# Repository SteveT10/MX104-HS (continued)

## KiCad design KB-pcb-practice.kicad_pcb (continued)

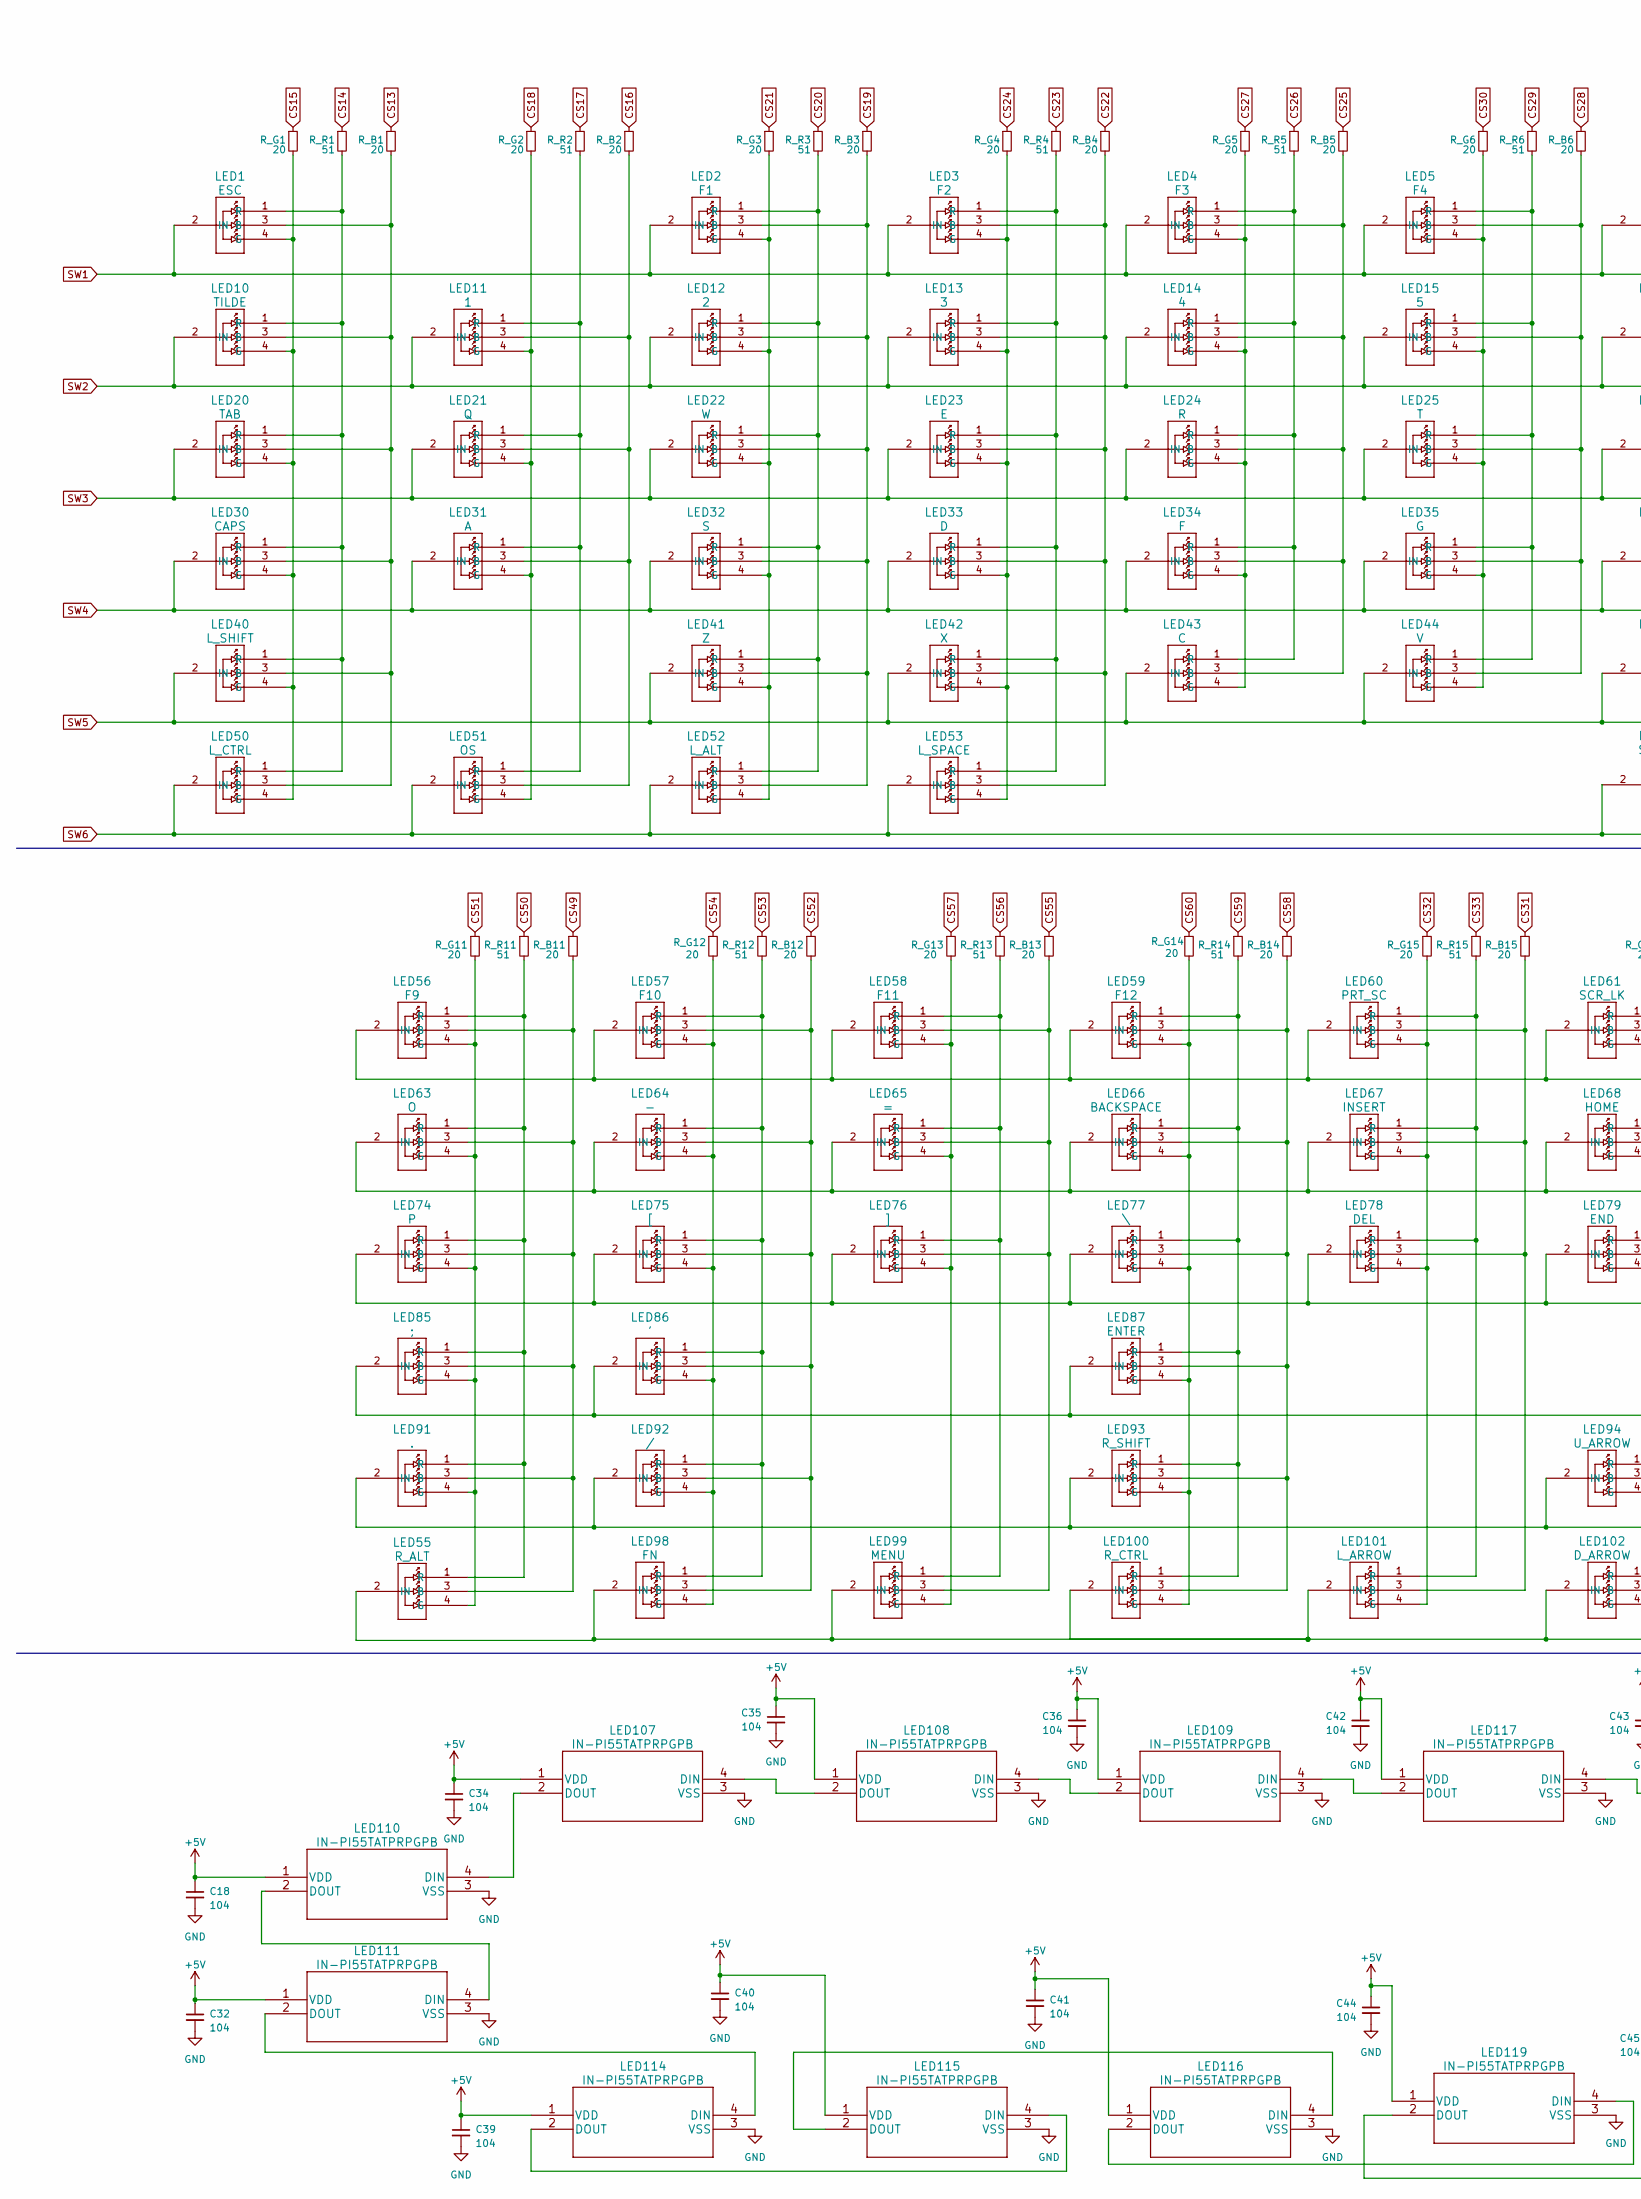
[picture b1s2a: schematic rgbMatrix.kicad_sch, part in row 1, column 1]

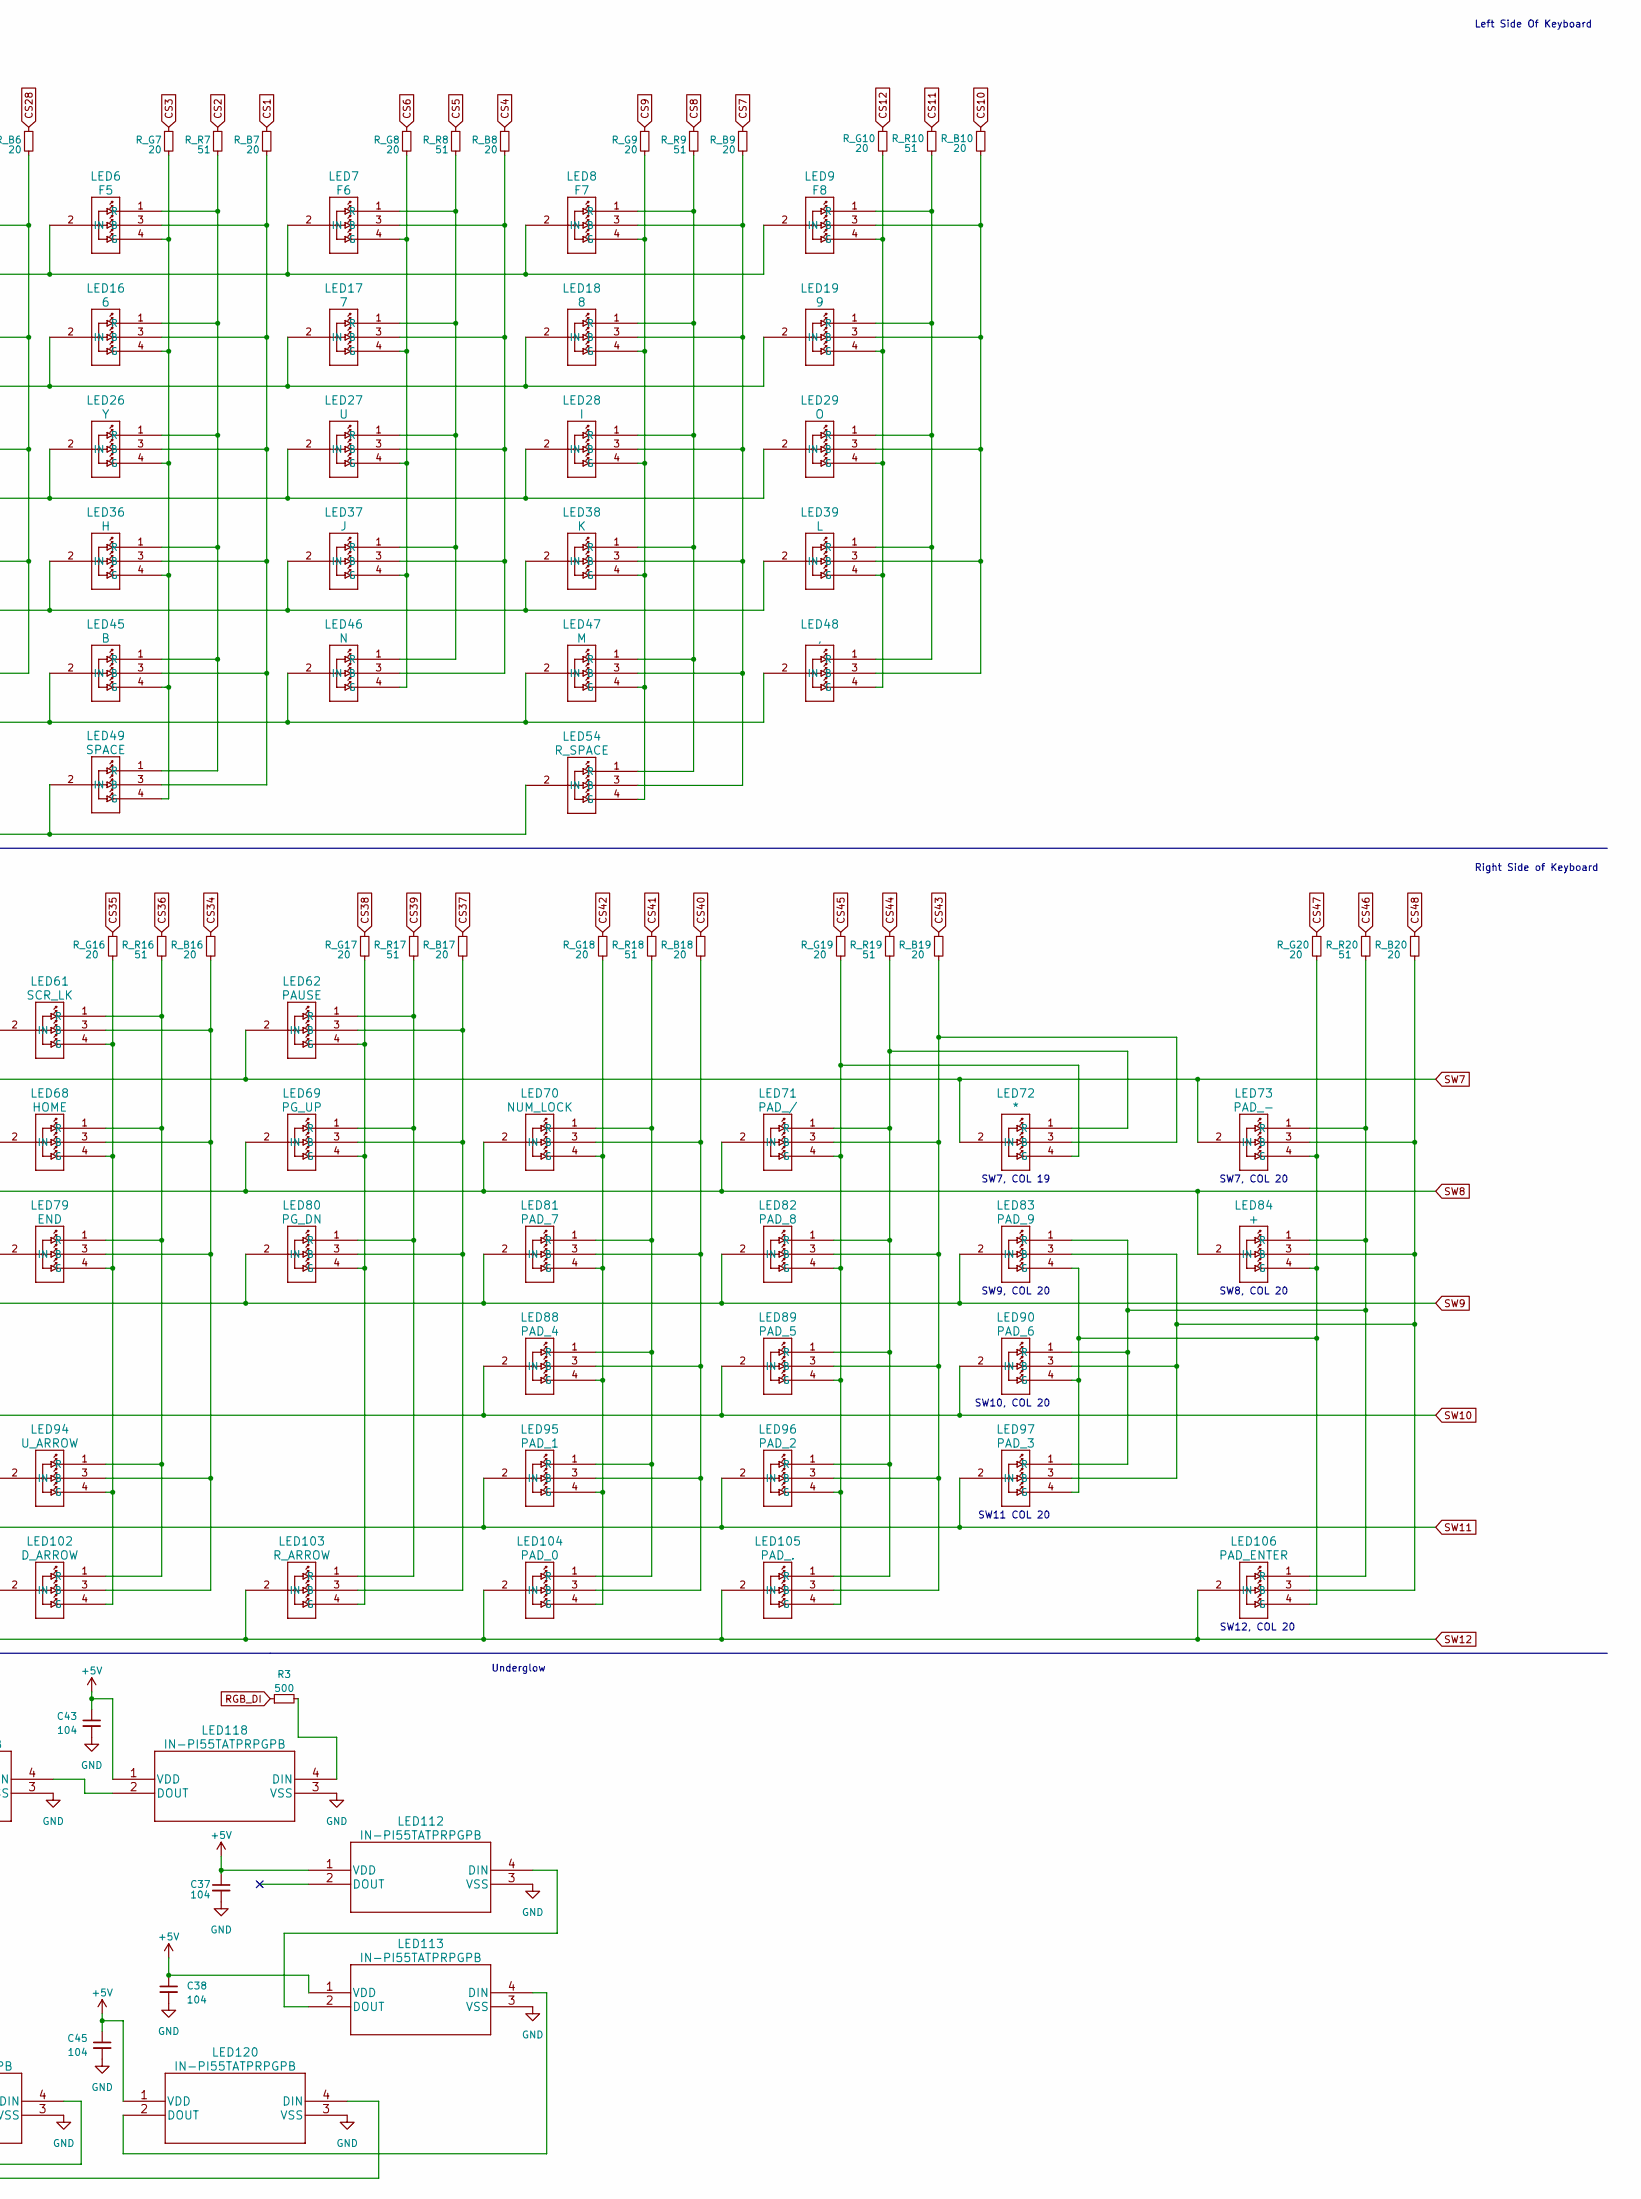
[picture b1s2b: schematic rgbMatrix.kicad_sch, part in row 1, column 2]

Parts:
C18, C32, C34, C35, C36, C37, C38, C39, C40, C41, C42, C43, C44, C45: 104; C_0805_2012Metric_Pad1.18x1.45mm_HandSolder
LED1: ESC; PLCC4_SMD-LED_3p2X2p8_SLD
LED2: F1; PLCC4_SMD-LED_3p2X2p8_SLD
LED3: F2; PLCC4_SMD-LED_3p2X2p8_SLD
LED4: F3; PLCC4_SMD-LED_3p2X2p8_SLD
LED5: F4; PLCC4_SMD-LED_3p2X2p8_SLD
LED6: F5; PLCC4_SMD-LED_3p2X2p8_SLD
LED7: F6; PLCC4_SMD-LED_3p2X2p8_SLD
LED8: F7; PLCC4_SMD-LED_3p2X2p8_SLD
LED9: F8; PLCC4_SMD-LED_3p2X2p8_SLD
LED10: TILDE; PLCC4_SMD-LED_3p2X2p8_SLD
LED11: 1; PLCC4_SMD-LED_3p2X2p8_SLD
LED12: 2; PLCC4_SMD-LED_3p2X2p8_SLD
LED13: 3; PLCC4_SMD-LED_3p2X2p8_SLD
LED14: 4; PLCC4_SMD-LED_3p2X2p8_SLD
LED15: 5; PLCC4_SMD-LED_3p2X2p8_SLD
LED16: 6; PLCC4_SMD-LED_3p2X2p8_SLD
LED17: 7; PLCC4_SMD-LED_3p2X2p8_SLD
LED18: 8; PLCC4_SMD-LED_3p2X2p8_SLD
LED19: 9; PLCC4_SMD-LED_3p2X2p8_SLD
LED20: TAB; PLCC4_SMD-LED_3p2X2p8_SLD
LED21: Q; PLCC4_SMD-LED_3p2X2p8_SLD
LED22: W; PLCC4_SMD-LED_3p2X2p8_SLD
LED23: E; PLCC4_SMD-LED_3p2X2p8_SLD
LED24: R; PLCC4_SMD-LED_3p2X2p8_SLD
LED25: T; PLCC4_SMD-LED_3p2X2p8_SLD
LED26: Y; PLCC4_SMD-LED_3p2X2p8_SLD
LED27: U; PLCC4_SMD-LED_3p2X2p8_SLD
LED28: I; PLCC4_SMD-LED_3p2X2p8_SLD
LED29, LED63: O; PLCC4_SMD-LED_3p2X2p8_SLD
LED30: CAPS; PLCC4_SMD-LED_3p2X2p8_SLD
LED31: A; PLCC4_SMD-LED_3p2X2p8_SLD
LED32: S; PLCC4_SMD-LED_3p2X2p8_SLD
LED33: D; PLCC4_SMD-LED_3p2X2p8_SLD
LED34: F; PLCC4_SMD-LED_3p2X2p8_SLD
LED35: G; PLCC4_SMD-LED_3p2X2p8_SLD
LED36: H; PLCC4_SMD-LED_3p2X2p8_SLD
LED37: J; PLCC4_SMD-LED_3p2X2p8_SLD
LED38: K; PLCC4_SMD-LED_3p2X2p8_SLD
LED39: L; PLCC4_SMD-LED_3p2X2p8_SLD
LED40: L_SHIFT; PLCC4_SMD-LED_3p2X2p8_SLD
LED41: Z; PLCC4_SMD-LED_3p2X2p8_SLD
LED42: X; PLCC4_SMD-LED_3p2X2p8_SLD
LED43: C; PLCC4_SMD-LED_3p2X2p8_SLD
LED44: V; PLCC4_SMD-LED_3p2X2p8_SLD
LED45: B; PLCC4_SMD-LED_3p2X2p8_SLD
LED46: N; PLCC4_SMD-LED_3p2X2p8_SLD
LED47: M; PLCC4_SMD-LED_3p2X2p8_SLD
LED48: ,; PLCC4_SMD-LED_3p2X2p8_SLD
LED49: SPACE; PLCC4_SMD-LED_3p2X2p8_SLD
LED50: L_CTRL; PLCC4_SMD-LED_3p2X2p8_SLD
LED51: OS; PLCC4_SMD-LED_3p2X2p8_SLD
LED52: L_ALT; PLCC4_SMD-LED_3p2X2p8_SLD
LED53: L_SPACE; PLCC4_SMD-LED_3p2X2p8_SLD
LED54: R_SPACE; PLCC4_SMD-LED_3p2X2p8_SLD
LED55: R_ALT; PLCC4_SMD-LED_3p2X2p8_SLD
LED56: F9; PLCC4_SMD-LED_3p2X2p8_SLD
LED57: F10; PLCC4_SMD-LED_3p2X2p8_SLD
LED58: F11; PLCC4_SMD-LED_3p2X2p8_SLD
LED59: F12; PLCC4_SMD-LED_3p2X2p8_SLD
LED60: PRT_SC; PLCC4_SMD-LED_3p2X2p8_SLD
LED61: SCR_LK; PLCC4_SMD-LED_3p2X2p8_SLD
LED62: PAUSE; PLCC4_SMD-LED_3p2X2p8_SLD
LED64: -; PLCC4_SMD-LED_3p2X2p8_SLD
LED65: =; PLCC4_SMD-LED_3p2X2p8_SLD
LED66: BACKSPACE; PLCC4_SMD-LED_3p2X2p8_SLD
LED67: INSERT; PLCC4_SMD-LED_3p2X2p8_SLD
LED68: HOME; PLCC4_SMD-LED_3p2X2p8_SLD
LED69: PG_UP; PLCC4_SMD-LED_3p2X2p8_SLD
LED70: NUM_LOCK; PLCC4_SMD-LED_3p2X2p8_SLD
LED71: PAD_/; PLCC4_SMD-LED_3p2X2p8_SLD
LED72: *; PLCC4_SMD-LED_3p2X2p8_SLD
LED73: PAD_-; PLCC4_SMD-LED_3p2X2p8_SLD
LED74: P; PLCC4_SMD-LED_3p2X2p8_SLD
LED75: [; PLCC4_SMD-LED_3p2X2p8_SLD
LED76: ]; PLCC4_SMD-LED_3p2X2p8_SLD
LED77: \; PLCC4_SMD-LED_3p2X2p8_SLD
LED78: DEL; PLCC4_SMD-LED_3p2X2p8_SLD
LED79: END; PLCC4_SMD-LED_3p2X2p8_SLD
LED80: PG_DN; PLCC4_SMD-LED_3p2X2p8_SLD
LED81: PAD_7; PLCC4_SMD-LED_3p2X2p8_SLD
LED82: PAD_8; PLCC4_SMD-LED_3p2X2p8_SLD
LED83: PAD_9; PLCC4_SMD-LED_3p2X2p8_SLD
LED84: +; PLCC4_SMD-LED_3p2X2p8_SLD
LED85: ;; PLCC4_SMD-LED_3p2X2p8_SLD
LED86: '; PLCC4_SMD-LED_3p2X2p8_SLD
LED87: ENTER; PLCC4_SMD-LED_3p2X2p8_SLD
LED88: PAD_4; PLCC4_SMD-LED_3p2X2p8_SLD
LED89: PAD_5; PLCC4_SMD-LED_3p2X2p8_SLD
LED90: PAD_6; PLCC4_SMD-LED_3p2X2p8_SLD
LED91: .; PLCC4_SMD-LED_3p2X2p8_SLD
LED92: /; PLCC4_SMD-LED_3p2X2p8_SLD
LED93: R_SHIFT; PLCC4_SMD-LED_3p2X2p8_SLD
LED94: U_ARROW; PLCC4_SMD-LED_3p2X2p8_SLD
LED95: PAD_1; PLCC4_SMD-LED_3p2X2p8_SLD
LED96: PAD_2; PLCC4_SMD-LED_3p2X2p8_SLD
LED97: PAD_3; PLCC4_SMD-LED_3p2X2p8_SLD
LED98: FN; PLCC4_SMD-LED_3p2X2p8_SLD
LED99: MENU; PLCC4_SMD-LED_3p2X2p8_SLD
LED100: R_CTRL; PLCC4_SMD-LED_3p2X2p8_SLD
LED101: L_ARROW; PLCC4_SMD-LED_3p2X2p8_SLD
LED102: D_ARROW; PLCC4_SMD-LED_3p2X2p8_SLD
LED103: R_ARROW; PLCC4_SMD-LED_3p2X2p8_SLD
LED104: PAD_0; PLCC4_SMD-LED_3p2X2p8_SLD
LED105: PAD_.; PLCC4_SMD-LED_3p2X2p8_SLD
LED106: PAD_ENTER; PLCC4_SMD-LED_3p2X2p8_SLD
LED107, LED108, LED109, LED110, LED111, LED112, LED113, LED114, LED115, LED116, LED117, LED118, LED119, LED120: IN-PI55TATPRPGPB
R3: 500; R_0805_2012Metric_Pad1.20x1.40mm_HandSolder
R_B1, R_B2, R_B3, R_B4, R_B5, R_B6, R_B7, R_B8, R_B9, R_B10, R_B11, R_B12, R_B13, R_B14, R_B15, R_B16, R_B17, R_B18, R_B19, R_B20: 20; R_0805_2012Metric_Pad1.20x1.40mm_HandSolder
R_G1, R_G2, R_G3, R_G4, R_G5, R_G6, R_G7, R_G8, R_G9, R_G10, R_G11, R_G12, R_G13, R_G14, R_G15, R_G16, R_G17, R_G18, R_G19, R_G20: 20; R_0805_2012Metric_Pad1.20x1.40mm_HandSolder
R_R1, R_R2, R_R3, R_R4, R_R5, R_R6, R_R7, R_R8, R_R9, R_R10, R_R11, R_R12, R_R13, R_R14, R_R15, R_R16, R_R17, R_R18, R_R19, R_R20: 51; R_0805_2012Metric_Pad1.20x1.40mm_HandSolder

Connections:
+5V: C18.1, C32.1, C34.1, C35.1, C36.1, C37.1, C38.1, C39.1, C40.1, C41.1, C42.1, C43.1, C44.1, C45.1, LED107.1 (VDD), LED108.1 (VDD), LED109.1 (VDD), LED110.1 (VDD), LED111.1 (VDD), LED112.1 (VDD), LED113.1 (VDD), LED114.1 (VDD), LED115.1 (VDD), LED116.1 (VDD), LED117.1 (VDD), LED118.1 (VDD), LED119.1 (VDD), LED120.1 (VDD); also elsewhere on the board
CS1: R_B7.1; also elsewhere on the board
CS2: R_R7.1; also elsewhere on the board
CS3: R_G7.1; also elsewhere on the board
CS4: R_B8.1; also elsewhere on the board
CS5: R_R8.1; also elsewhere on the board
CS6: R_G8.1; also elsewhere on the board
CS7: R_B9.1; also elsewhere on the board
CS8: R_R9.1; also elsewhere on the board
CS9: R_G9.1; also elsewhere on the board
CS10: R_B10.1; also elsewhere on the board
CS11: R_R10.1; also elsewhere on the board
CS12: R_G10.1; also elsewhere on the board
CS13: R_B1.1; also elsewhere on the board
CS14: R_R1.1; also elsewhere on the board
CS15: R_G1.1; also elsewhere on the board
CS16: R_B2.1; also elsewhere on the board
CS17: R_R2.1; also elsewhere on the board
CS18: R_G2.1; also elsewhere on the board
CS19: R_B3.1; also elsewhere on the board
CS20: R_R3.1; also elsewhere on the board
CS21: R_G3.1; also elsewhere on the board
CS22: R_B4.1; also elsewhere on the board
CS23: R_R4.1; also elsewhere on the board
CS24: R_G4.1; also elsewhere on the board
CS25: R_B5.1; also elsewhere on the board
CS26: R_R5.1; also elsewhere on the board
CS27: R_G5.1; also elsewhere on the board
CS28: R_B6.1; also elsewhere on the board
CS29: R_R6.1; also elsewhere on the board
CS30: R_G6.1; also elsewhere on the board
CS31: R_B15.1; also elsewhere on the board
CS32: R_G15.1; also elsewhere on the board
CS33: R_R15.1; also elsewhere on the board
CS34: R_B16.1; also elsewhere on the board
CS35: R_G16.1; also elsewhere on the board
CS36: R_R16.1; also elsewhere on the board
CS37: R_B17.1; also elsewhere on the board
CS38: R_G17.1; also elsewhere on the board
CS39: R_R17.1; also elsewhere on the board
CS40: R_B18.1; also elsewhere on the board
CS41: R_R18.1; also elsewhere on the board
CS42: R_G18.1; also elsewhere on the board
CS43: R_B19.1; also elsewhere on the board
CS44: R_R19.1; also elsewhere on the board
CS45: R_G19.1; also elsewhere on the board
CS46: R_R20.1; also elsewhere on the board
CS47: R_G20.1; also elsewhere on the board
CS48: R_B20.1; also elsewhere on the board
CS49: R_B11.1; also elsewhere on the board
CS50: R_R11.1; also elsewhere on the board
CS51: R_G11.1; also elsewhere on the board
CS52: R_B12.1; also elsewhere on the board
CS53: R_R12.1; also elsewhere on the board
CS54: R_G12.1; also elsewhere on the board
CS55: R_B13.1; also elsewhere on the board
CS56: R_R13.1; also elsewhere on the board
CS57: R_G13.1; also elsewhere on the board
CS58: R_B14.1; also elsewhere on the board
CS59: R_R14.1; also elsewhere on the board
CS60: R_G14.1; also elsewhere on the board
GND: C18.2, C32.2, C34.2, C35.2, C36.2, C37.2, C38.2, C39.2, C40.2, C41.2, C42.2, C43.2, C44.2, C45.2, LED107.3 (VSS), LED108.3 (VSS), LED109.3 (VSS), LED110.3 (VSS), LED111.3 (VSS), LED112.3 (VSS), LED113.3 (VSS), LED114.3 (VSS), LED115.3 (VSS), LED116.3 (VSS), LED117.3 (VSS), LED118.3 (VSS), LED119.3 (VSS), LED120.3 (VSS); also elsewhere on the board
unnamed: LED1.3 (B), LED10.3 (B), LED20.3 (B), LED30.3 (B), LED40.3 (B), LED50.3 (B), R_B1.2
unnamed: LED1.4 (G), LED10.4 (G), LED20.4 (G), LED30.4 (G), LED40.4 (G), LED50.4 (G), R_G1.2
unnamed: LED1.1 (R), LED10.1 (R), LED20.1 (R), LED30.1 (R), LED40.1 (R), LED50.1 (R), R_R1.2
unnamed: LED11.3 (B), LED21.3 (B), LED31.3 (B), LED51.3 (B), R_B2.2
unnamed: LED11.4 (G), LED21.4 (G), LED31.4 (G), LED51.4 (G), R_G2.2
unnamed: LED11.1 (R), LED21.1 (R), LED31.1 (R), LED51.1 (R), R_R2.2
unnamed: LED2.3 (B), LED12.3 (B), LED22.3 (B), LED32.3 (B), LED41.3 (B), LED52.3 (B), R_B3.2
unnamed: LED2.4 (G), LED12.4 (G), LED22.4 (G), LED32.4 (G), LED41.4 (G), LED52.4 (G), R_G3.2
unnamed: LED2.1 (R), LED12.1 (R), LED22.1 (R), LED32.1 (R), LED41.1 (R), LED52.1 (R), R_R3.2
unnamed: LED3.3 (B), LED13.3 (B), LED23.3 (B), LED33.3 (B), LED42.3 (B), LED53.3 (B), R_B4.2
unnamed: LED3.4 (G), LED13.4 (G), LED23.4 (G), LED33.4 (G), LED42.4 (G), LED53.4 (G), R_G4.2
unnamed: LED3.1 (R), LED13.1 (R), LED23.1 (R), LED33.1 (R), LED42.1 (R), LED53.1 (R), R_R4.2
unnamed: LED4.3 (B), LED14.3 (B), LED24.3 (B), LED34.3 (B), LED43.3 (B), R_B5.2
unnamed: LED4.4 (G), LED14.4 (G), LED24.4 (G), LED34.4 (G), LED43.4 (G), R_G5.2
unnamed: LED4.1 (R), LED14.1 (R), LED24.1 (R), LED34.1 (R), LED43.1 (R), R_R5.2
unnamed: LED5.3 (B), LED15.3 (B), LED25.3 (B), LED35.3 (B), LED44.3 (B), R_B6.2
unnamed: LED5.4 (G), LED15.4 (G), LED25.4 (G), LED35.4 (G), LED44.4 (G), R_G6.2
unnamed: LED5.1 (R), LED15.1 (R), LED25.1 (R), LED35.1 (R), LED44.1 (R), R_R6.2
unnamed: LED6.3 (B), LED16.3 (B), LED26.3 (B), LED36.3 (B), LED45.3 (B), LED49.3 (B), R_B7.2
unnamed: LED6.4 (G), LED16.4 (G), LED26.4 (G), LED36.4 (G), LED45.4 (G), LED49.4 (G), R_G7.2
unnamed: LED6.1 (R), LED16.1 (R), LED26.1 (R), LED36.1 (R), LED45.1 (R), LED49.1 (R), R_R7.2
unnamed: LED7.3 (B), LED17.3 (B), LED27.3 (B), LED37.3 (B), LED46.3 (B), R_B8.2
unnamed: LED7.4 (G), LED17.4 (G), LED27.4 (G), LED37.4 (G), LED46.4 (G), R_G8.2
unnamed: LED7.1 (R), LED17.1 (R), LED27.1 (R), LED37.1 (R), LED46.1 (R), R_R8.2
unnamed: LED8.3 (B), LED18.3 (B), LED28.3 (B), LED38.3 (B), LED47.3 (B), LED54.3 (B), R_B9.2
unnamed: LED8.4 (G), LED18.4 (G), LED28.4 (G), LED38.4 (G), LED47.4 (G), LED54.4 (G), R_G9.2
unnamed: LED8.1 (R), LED18.1 (R), LED28.1 (R), LED38.1 (R), LED47.1 (R), LED54.1 (R), R_R9.2
unnamed: LED9.3 (B), LED19.3 (B), LED29.3 (B), LED39.3 (B), LED48.3 (B), R_B10.2
unnamed: LED9.4 (G), LED19.4 (G), LED29.4 (G), LED39.4 (G), LED48.4 (G), R_G10.2
unnamed: LED9.1 (R), LED19.1 (R), LED29.1 (R), LED39.1 (R), LED48.1 (R), R_R10.2
unnamed: LED55.3 (B), LED56.3 (B), LED63.3 (B), LED74.3 (B), LED85.3 (B), LED91.3 (B), R_B11.2
unnamed: LED55.4 (G), LED56.4 (G), LED63.4 (G), LED74.4 (G), LED85.4 (G), LED91.4 (G), R_G11.2
unnamed: LED55.1 (R), LED56.1 (R), LED63.1 (R), LED74.1 (R), LED85.1 (R), LED91.1 (R), R_R11.2
unnamed: LED57.3 (B), LED64.3 (B), LED75.3 (B), LED86.3 (B), LED92.3 (B), LED98.3 (B), R_B12.2
unnamed: LED57.4 (G), LED64.4 (G), LED75.4 (G), LED86.4 (G), LED92.4 (G), LED98.4 (G), R_G12.2
unnamed: LED57.1 (R), LED64.1 (R), LED75.1 (R), LED86.1 (R), LED92.1 (R), LED98.1 (R), R_R12.2
unnamed: LED58.3 (B), LED65.3 (B), LED76.3 (B), LED99.3 (B), R_B13.2
unnamed: LED58.4 (G), LED65.4 (G), LED76.4 (G), LED99.4 (G), R_G13.2
unnamed: LED58.1 (R), LED65.1 (R), LED76.1 (R), LED99.1 (R), R_R13.2
unnamed: LED59.3 (B), LED66.3 (B), LED77.3 (B), LED87.3 (B), LED93.3 (B), LED100.3 (B), R_B14.2
unnamed: LED59.4 (G), LED66.4 (G), LED77.4 (G), LED87.4 (G), LED93.4 (G), LED100.4 (G), R_G14.2
unnamed: LED59.1 (R), LED66.1 (R), LED77.1 (R), LED87.1 (R), LED93.1 (R), LED100.1 (R), R_R14.2
unnamed: LED60.3 (B), LED67.3 (B), LED78.3 (B), LED101.3 (B), R_B15.2
unnamed: LED60.4 (G), LED67.4 (G), LED78.4 (G), LED101.4 (G), R_G15.2
unnamed: LED60.1 (R), LED67.1 (R), LED78.1 (R), LED101.1 (R), R_R15.2
unnamed: LED61.3 (B), LED68.3 (B), LED79.3 (B), LED94.3 (B), LED102.3 (B), R_B16.2
unnamed: LED61.4 (G), LED68.4 (G), LED79.4 (G), LED94.4 (G), LED102.4 (G), R_G16.2
unnamed: LED61.1 (R), LED68.1 (R), LED79.1 (R), LED94.1 (R), LED102.1 (R), R_R16.2
unnamed: LED62.3 (B), LED69.3 (B), LED80.3 (B), LED103.3 (B), R_B17.2
unnamed: LED62.4 (G), LED69.4 (G), LED80.4 (G), LED103.4 (G), R_G17.2
unnamed: LED62.1 (R), LED69.1 (R), LED80.1 (R), LED103.1 (R), R_R17.2
unnamed: LED70.3 (B), LED81.3 (B), LED88.3 (B), LED95.3 (B), LED104.3 (B), R_B18.2
unnamed: LED70.4 (G), LED81.4 (G), LED88.4 (G), LED95.4 (G), LED104.4 (G), R_G18.2
unnamed: LED70.1 (R), LED81.1 (R), LED88.1 (R), LED95.1 (R), LED104.1 (R), R_R18.2
unnamed: LED71.3 (B), LED72.3 (B), LED82.3 (B), LED89.3 (B), LED96.3 (B), LED105.3 (B), R_B19.2
unnamed: LED71.4 (G), LED72.4 (G), LED82.4 (G), LED89.4 (G), LED96.4 (G), LED105.4 (G), R_G19.2
unnamed: LED71.1 (R), LED72.1 (R), LED82.1 (R), LED89.1 (R), LED96.1 (R), LED105.1 (R), R_R19.2
unnamed: LED73.3 (B), LED83.3 (B), LED84.3 (B), LED90.3 (B), LED97.3 (B), LED106.3 (B), R_B20.2
unnamed: LED73.4 (G), LED83.4 (G), LED84.4 (G), LED90.4 (G), LED97.4 (G), LED106.4 (G), R_G20.2
unnamed: LED73.1 (R), LED83.1 (R), LED84.1 (R), LED90.1 (R), LED97.1 (R), LED106.1 (R), R_R20.2
unnamed: LED107.4 (DIN), LED108.2 (DOUT)
unnamed: LED107.2 (DOUT), LED110.4 (DIN)
unnamed: LED108.4 (DIN), LED109.2 (DOUT)
unnamed: LED109.4 (DIN), LED117.2 (DOUT)
unnamed: LED110.2 (DOUT), LED111.4 (DIN)
unnamed: LED111.2 (DOUT), LED114.4 (DIN)
unnamed: LED112.4 (DIN), LED113.2 (DOUT)
unnamed: LED113.4 (DIN), LED120.2 (DOUT)
unnamed: LED114.2 (DOUT), LED115.4 (DIN)
unnamed: LED115.2 (DOUT), LED116.4 (DIN)
unnamed: LED116.2 (DOUT), LED119.4 (DIN)
unnamed: LED117.4 (DIN), LED118.2 (DOUT)
unnamed: LED118.4 (DIN), R3.2
unnamed: LED119.2 (DOUT), LED120.4 (DIN)
RGB_DI: R3.1; also elsewhere on the board
SW1: LED1.2 (IN), LED2.2 (IN), LED3.2 (IN), LED4.2 (IN), LED5.2 (IN), LED6.2 (IN), LED7.2 (IN), LED8.2 (IN), LED9.2 (IN); also elsewhere on the board
SW2: LED10.2 (IN), LED11.2 (IN), LED12.2 (IN), LED13.2 (IN), LED14.2 (IN), LED15.2 (IN), LED16.2 (IN), LED17.2 (IN), LED18.2 (IN), LED19.2 (IN); also elsewhere on the board
SW3: LED20.2 (IN), LED21.2 (IN), LED22.2 (IN), LED23.2 (IN), LED24.2 (IN), LED25.2 (IN), LED26.2 (IN), LED27.2 (IN), LED28.2 (IN), LED29.2 (IN); also elsewhere on the board
SW4: LED30.2 (IN), LED31.2 (IN), LED32.2 (IN), LED33.2 (IN), LED34.2 (IN), LED35.2 (IN), LED36.2 (IN), LED37.2 (IN), LED38.2 (IN), LED39.2 (IN); also elsewhere on the board
SW5: LED40.2 (IN), LED41.2 (IN), LED42.2 (IN), LED43.2 (IN), LED44.2 (IN), LED45.2 (IN), LED46.2 (IN), LED47.2 (IN), LED48.2 (IN); also elsewhere on the board
SW6: LED49.2 (IN), LED50.2 (IN), LED51.2 (IN), LED52.2 (IN), LED53.2 (IN), LED54.2 (IN); also elsewhere on the board
SW7: LED56.2 (IN), LED57.2 (IN), LED58.2 (IN), LED59.2 (IN), LED60.2 (IN), LED61.2 (IN), LED62.2 (IN), LED72.2 (IN), LED73.2 (IN); also elsewhere on the board
SW8: LED63.2 (IN), LED64.2 (IN), LED65.2 (IN), LED66.2 (IN), LED67.2 (IN), LED68.2 (IN), LED69.2 (IN), LED70.2 (IN), LED71.2 (IN), LED84.2 (IN); also elsewhere on the board
SW9: LED74.2 (IN), LED75.2 (IN), LED76.2 (IN), LED77.2 (IN), LED78.2 (IN), LED79.2 (IN), LED80.2 (IN), LED81.2 (IN), LED82.2 (IN), LED83.2 (IN); also elsewhere on the board
SW10: LED85.2 (IN), LED86.2 (IN), LED87.2 (IN), LED88.2 (IN), LED89.2 (IN), LED90.2 (IN); also elsewhere on the board
SW11: LED91.2 (IN), LED92.2 (IN), LED93.2 (IN), LED94.2 (IN), LED95.2 (IN), LED96.2 (IN), LED97.2 (IN); also elsewhere on the board
SW12: LED55.2 (IN), LED98.2 (IN), LED99.2 (IN), LED100.2 (IN), LED101.2 (IN), LED102.2 (IN), LED103.2 (IN), LED104.2 (IN), LED105.2 (IN), LED106.2 (IN); also elsewhere on the board

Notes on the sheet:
SW8, COL 20
SW7, COL 19
SW11 COL 20
SW12, COL 20
SW10, COL 20
Right Side of Keyboard
Left Side Of Keyboard
Underglow
SW7, COL 20
SW9, COL 20
